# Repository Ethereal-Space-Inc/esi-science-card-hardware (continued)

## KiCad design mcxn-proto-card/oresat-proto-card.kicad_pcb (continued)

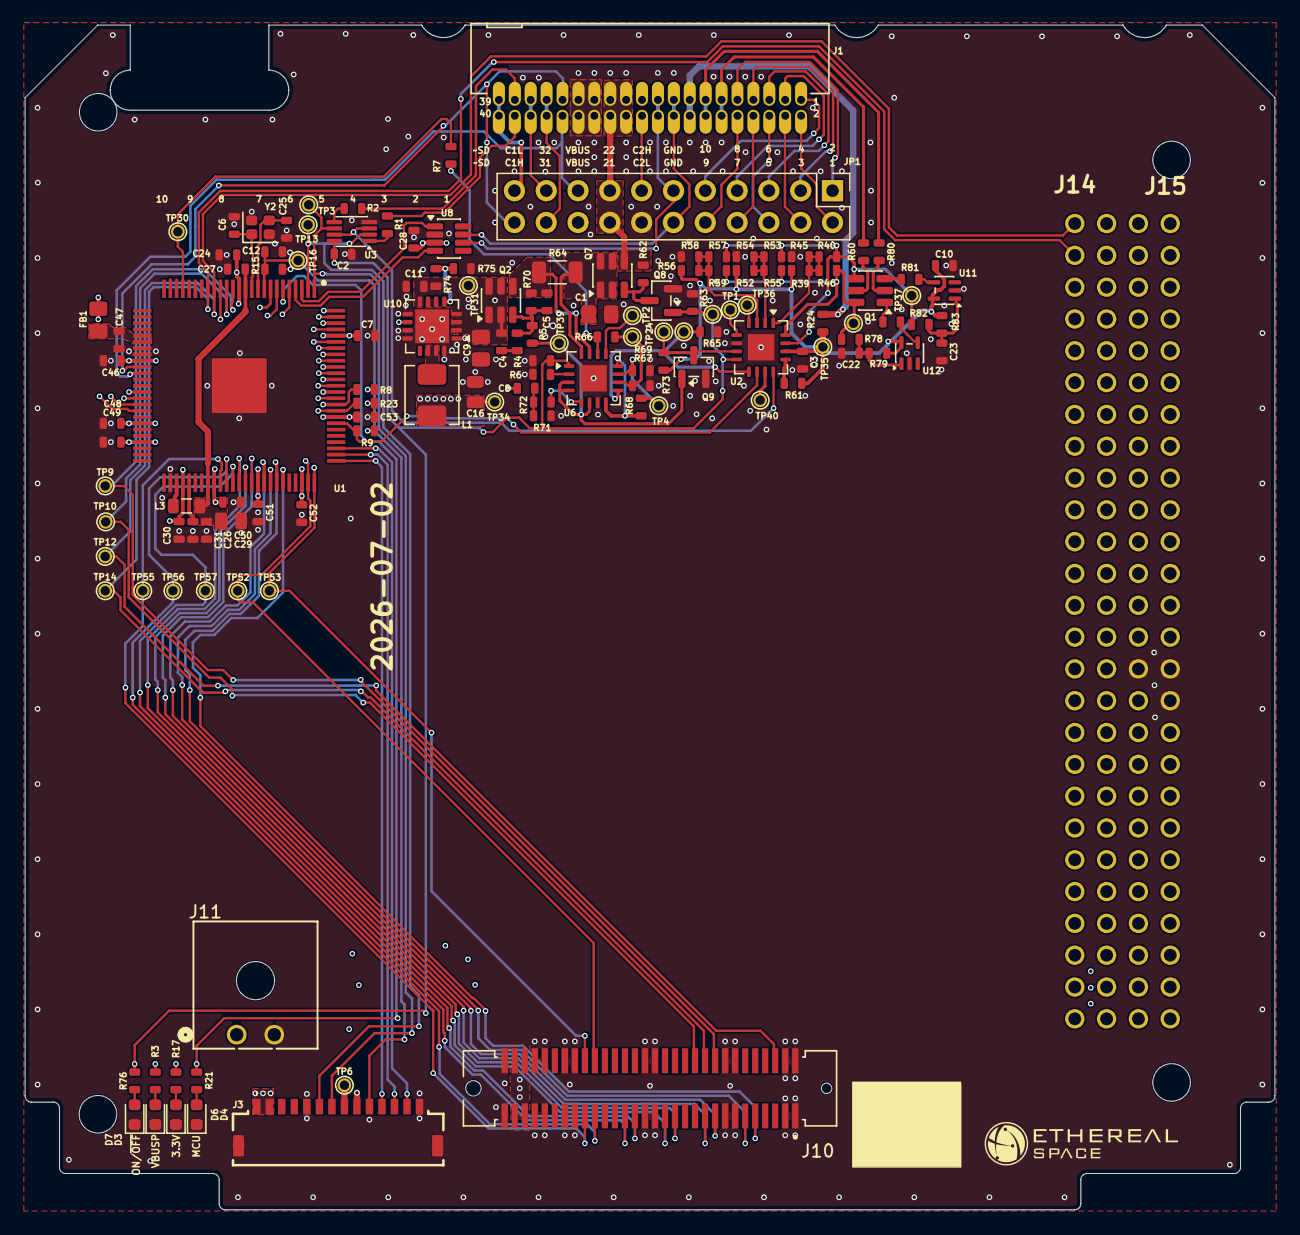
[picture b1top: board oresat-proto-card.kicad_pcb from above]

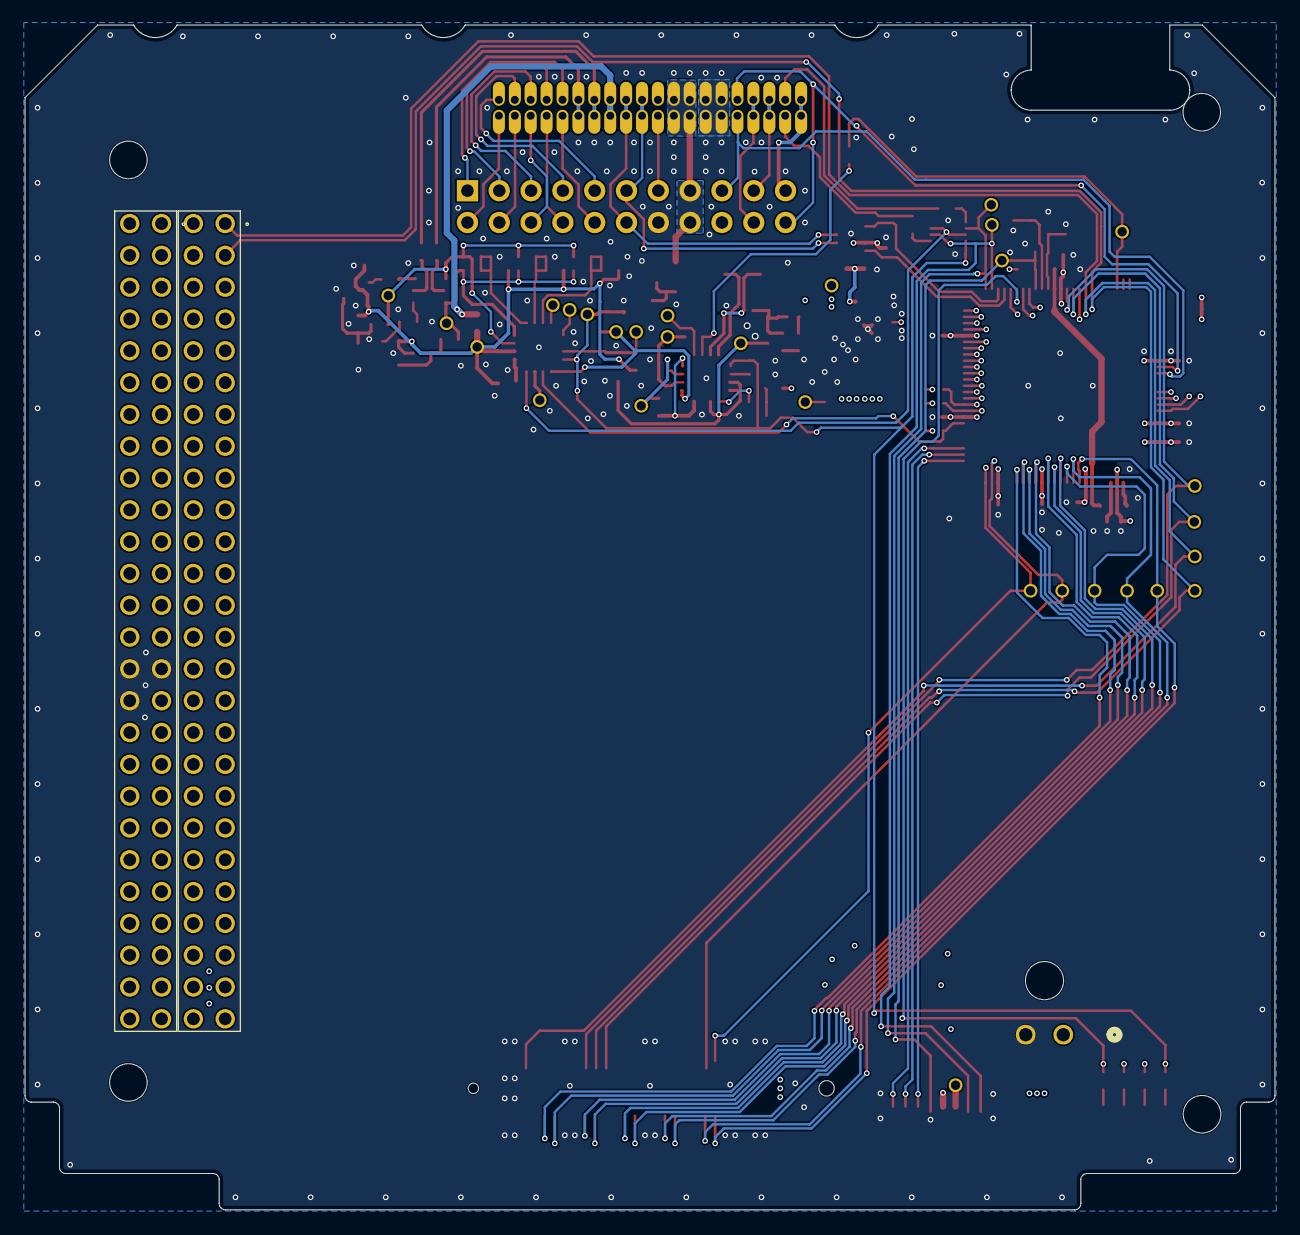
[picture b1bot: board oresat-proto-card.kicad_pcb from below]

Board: 4 copper layers, 99.8 x 94.6 mm, 140 parts (2 on the bottom side), 108 nets.

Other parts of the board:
JP1: PINHD-2X5; PinHeader_2x11_P2.54mm_Vertical

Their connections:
/CAN1_H: JP1.20; also elsewhere on the board
/CAN1_L: JP1.19; also elsewhere on the board
/CAN2_H: JP1.12; also elsewhere on the board
/CAN2_L: JP1.11; also elsewhere on the board
/Microcontroller/FC2_0: JP1.22; also elsewhere on the board
/Microcontroller/FC2_1: JP1.17; also elsewhere on the board
/SPARE1: JP1.9; also elsewhere on the board
/SPARE2: JP1.2; also elsewhere on the board
/SPARE3: JP1.7; also elsewhere on the board
/SPARE4: JP1.4; also elsewhere on the board
/SPARE5: JP1.5; also elsewhere on the board
/SPARE6: JP1.6; also elsewhere on the board
/SPARE7: JP1.3; also elsewhere on the board
/SPARE8: JP1.8; also elsewhere on the board
/SPARE9: JP1.1; also elsewhere on the board
/SPARE10: JP1.10; also elsewhere on the board
/SPARE21: JP1.18; also elsewhere on the board
/SPARE22: JP1.13; also elsewhere on the board
/~SD: JP1.21; also elsewhere on the board
GND: JP1.14; also elsewhere on the board
VBUS: JP1.15, JP1.16; also elsewhere on the board
